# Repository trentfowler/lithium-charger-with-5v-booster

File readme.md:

# Single-cell li-ion charger and 5v booster

**Description:** KiCad schematic and reference pcb layout for a Li-ion charging circuit 

- 5v input from micro-usb used to charge a single-cell lithium battery and supply 5v output voltage. 
- When wall supply is disconnected li-ion battery output goes through 5v boost converter and supplies 5v output voltage

**References:**
- MCP73831 li-ion charger - http://ww1.microchip.com/downloads/en/DeviceDoc/20001984g.pdf
- TPS61200DRC 5v booster - http://www.ti.com/lit/ds/symlink/tps61202.pdf

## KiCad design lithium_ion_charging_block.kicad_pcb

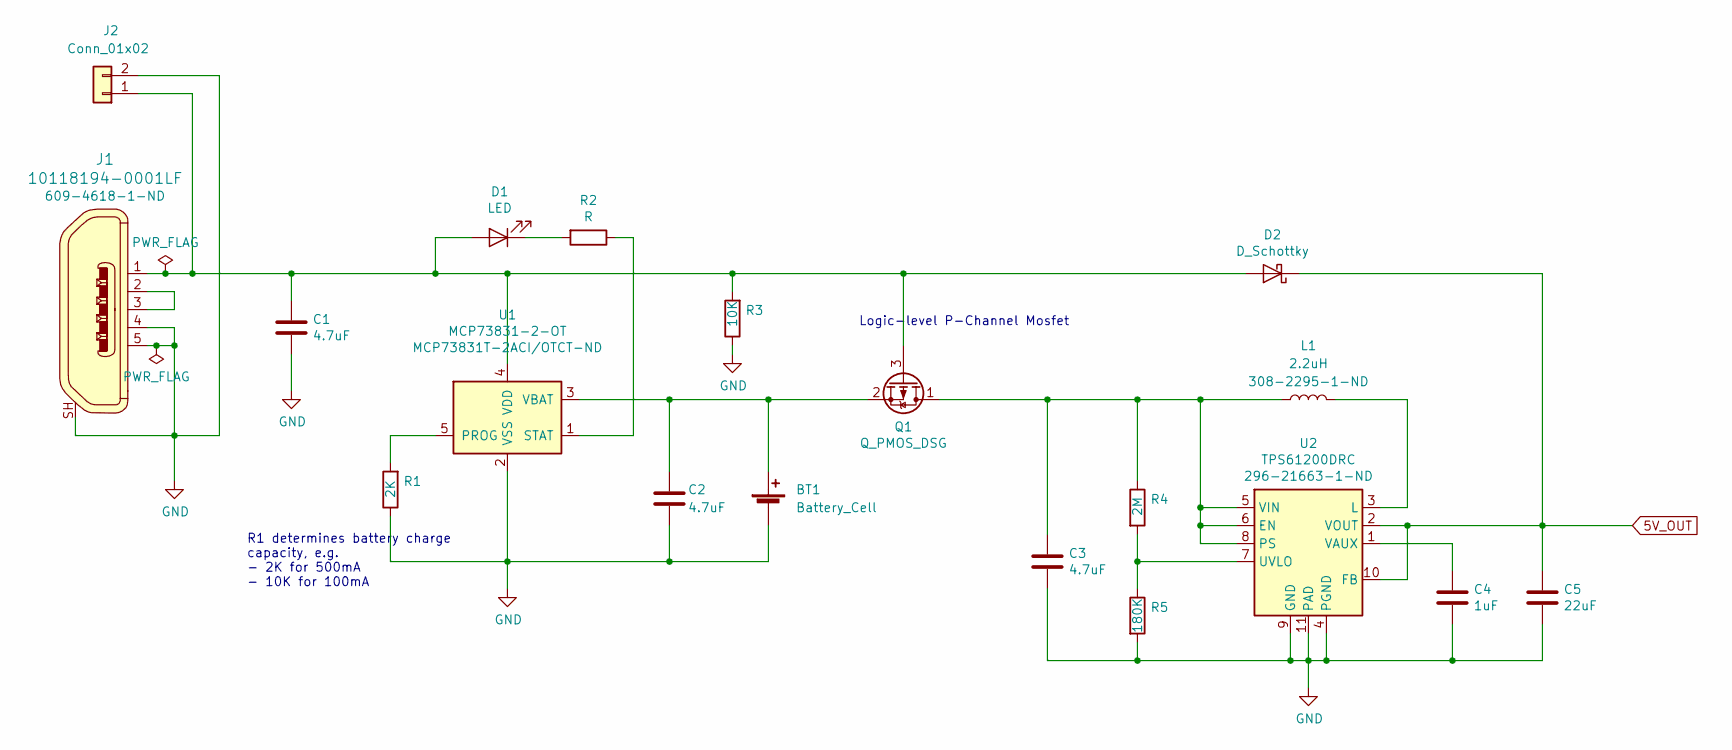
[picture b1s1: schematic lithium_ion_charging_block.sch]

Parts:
BT1: Battery_Cell; JST_XH_S2B-XH-A_1x02_P2.50mm_Horizontal
C1, C2, C3: 4.7uF; C_0805_2012Metric_Pad1.15x1.40mm_HandSolder
C4: 1uF; C_0805_2012Metric_Pad1.15x1.40mm_HandSolder
C5: 22uF; C_0805_2012Metric_Pad1.15x1.40mm_HandSolder
D1: LED; LED_0805_2012Metric_Pad1.15x1.40mm_HandSolder
D2: D_Schottky; D_0805_2012Metric_Pad1.15x1.40mm_HandSolder
J1: 10118194-0001LF; USB_Micro_B_Female_10118194-0001LF; MPN 10118194-0001LF; Digi-Key_PN 609-4618-1-ND
J2: Conn_01x02; TerminalBlock_bornier-2_P5.08mm
L1: 2.2uH; CDRH2D18; digikey 308-2295-1-ND
Q1: Q_PMOS_DSG; SOT-23_Handsoldering
R1: 2K; R_0805_2012Metric_Pad1.15x1.40mm_HandSolder
R2: R; R_0805_2012Metric_Pad1.15x1.40mm_HandSolder
R3: 10K; R_0805_2012Metric_Pad1.15x1.40mm_HandSolder
R4: 2M; R_0805_2012Metric_Pad1.15x1.40mm_HandSolder
R5: 180K; R_0805_2012Metric_Pad1.15x1.40mm_HandSolder
U1: MCP73831-2-OT; SOT-23-5; digikey MCP73831T-2ACI/OTCT-ND
U2: TPS61200DRC; Texas_S-PVSON-N10_ThermalVias; digikey 296-21663-1-ND

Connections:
5V_OUT: C5.1, D2.1 (K), U2.2 (VOUT), U2.10 (FB)
GND: BT1.2 (-), C1.2, C2.2, C3.2, C4.2, C5.2, J1.4, J1.5, J1.SH, J2.2, R1.1, R3.1, R5.2, U1.2 (VSS), U2.4 (PGND), U2.9 (GND), U2.11 (PAD)
unnamed: BT1.1 (+), C2.1, Q1.2 (S), U1.3 (VBAT)
unnamed: C1.1, D1.2 (A), D2.2 (A), J1.1, J2.1, Q1.3 (G), R3.2, U1.4 (VDD)
unnamed: C3.1, L1.1, Q1.1 (D), R4.1, U2.5 (VIN), U2.6 (EN), U2.8 (PS)
unnamed: C4.1, U2.1 (VAUX)
unnamed: D1.1 (K), R2.2
unnamed: J1.2, J1.3
unnamed: L1.2, U2.3 (L)
unnamed: R1.2, U1.5 (PROG)
unnamed: R2.1, U1.1 (STAT)
unnamed: R4.2, R5.1, U2.7 (UVLO)

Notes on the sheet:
R1 determines battery charge capacity, e.g. - 2K for 500mA - 10K for 100mA
Logic-level P-Channel Mosfet

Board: 2 copper layers, 19 parts (0 on the bottom side), 12 nets, no tracks yet.

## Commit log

2019-09-16 Added schematic and readme
2019-09-16 fix readme formatting
2019-09-16 fix readme title
